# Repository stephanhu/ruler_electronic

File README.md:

# ruler_electronic
A 30cm ruler with some electronic stuff

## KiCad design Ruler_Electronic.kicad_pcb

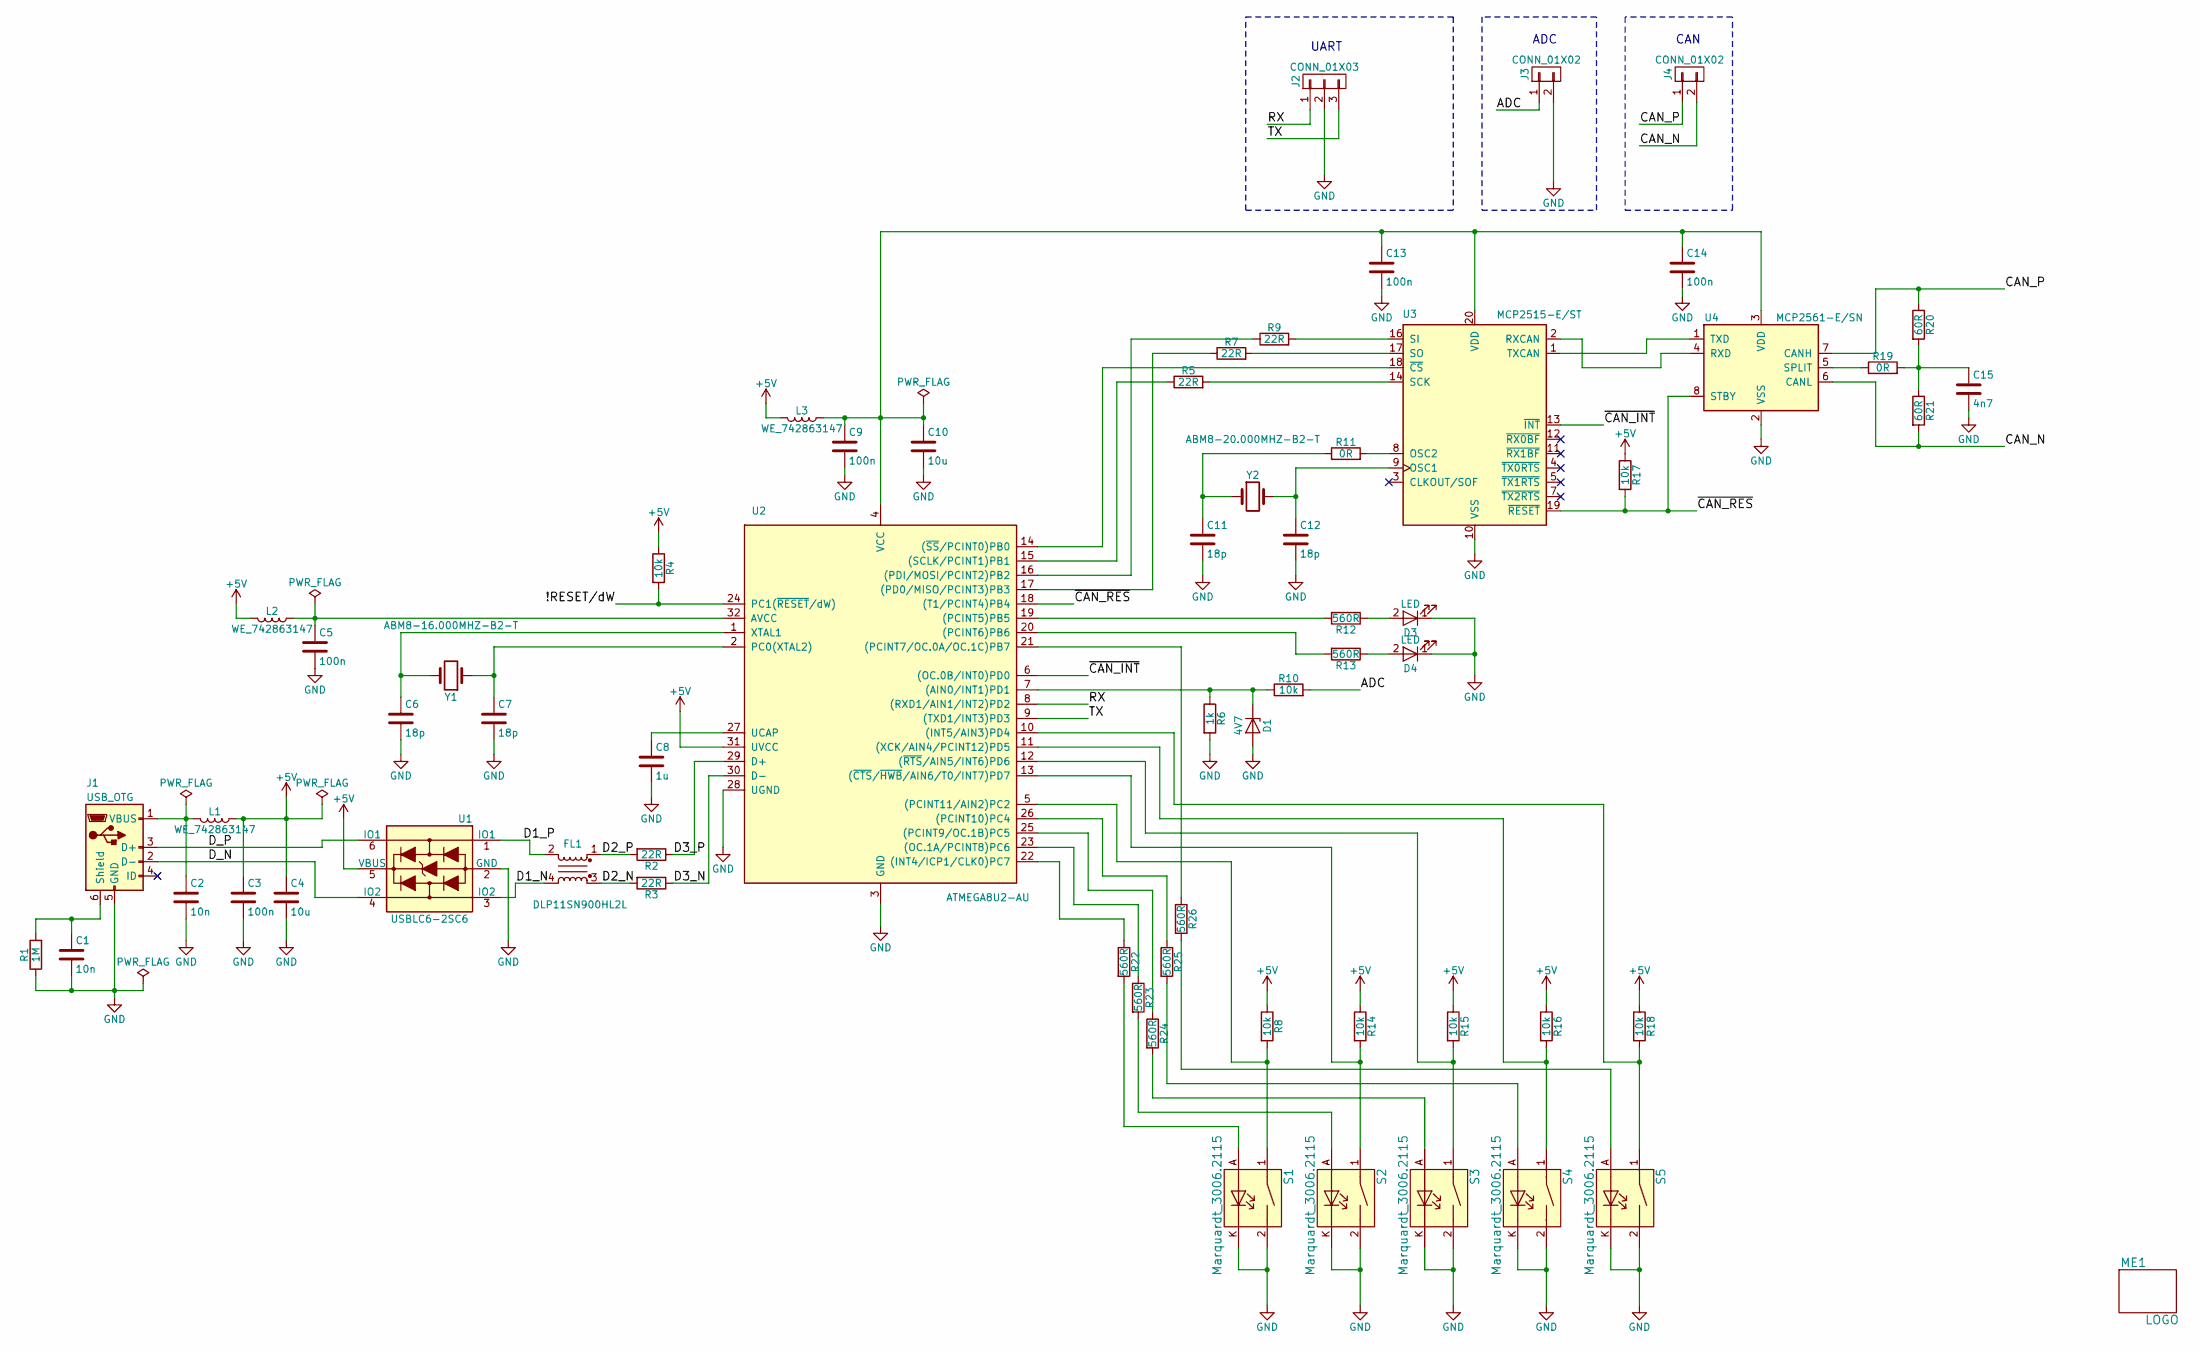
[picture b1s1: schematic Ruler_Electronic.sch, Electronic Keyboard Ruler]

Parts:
C1, C2: 10n; C_0603_HandSoldering
C3, C5, C9, C13, C14: 100n; C_0603_HandSoldering
C4, C10: 10u; C_0805_HandSoldering
C6, C7, C11, C12: 18p; C_0603_HandSoldering
C8: 1u; C_0805_HandSoldering
C15: 4n7; C_0603_HandSoldering
D1: 4V7; D_MELF_Handsoldering
D3, D4: LED; LED_0603_HandSoldering
FL1: DLP11SN900HL2L; L_Murata_DLP11S
J1: USB_OTG; USB_Mini-B
J2: CONN_01X03; Pin_Header_Angled_1x03_Pitch2.54mm
J3, J4: CONN_01X02; Pin_Header_Angled_1x02_Pitch2.54mm
L1, L2, L3: WE_742863147; L_0603_HandSoldering
ME1: LOGO; bytewerk_logo_15x13mm
R1: 1M; R_0603_HandSoldering
R2, R3, R5, R7, R9: 22R; R_0603_HandSoldering
R4, R8, R10, R14, R15, R16, R17, R18: 10k; R_0603_HandSoldering
R6: 1k; R_0603_HandSoldering
R11, R19: 0R; R_0603_HandSoldering
R12, R13, R22, R23, R24, R25, R26: 560R; R_0603_HandSoldering
R20, R21: 60R; R_0603_HandSoldering
S1, S2, S3, S4, S5: Marquardt_3006.2115; Marquardt_3006.2xxx
U1: USBLC6-2SC6; SOT-23-6
U2: ATMEGA8U2-AU; TQFP-32_7x7mm_Pitch0.8mm
U3: MCP2515-E/ST; TSSOP-20_4.4x6.5mm_Pitch0.65mm
U4: MCP2561-E/SN; SOIC-8_3.9x4.9mm_Pitch1.27mm
Y1: ABM8-16.000MHZ-B2-T; Crystal_SMD_Abracon_ABM8G-4pin_3.2x2.5mm
Y2: ABM8-20.000MHZ-B2-T; Crystal_SMD_Abracon_ABM8G-4pin_3.2x2.5mm

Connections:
+5V: C3.1, C4.1, L1.1, L2.2, L3.2, R4.1, R8.1, R14.1, R15.1, R16.1, R17.1, R18.1, U1.5 (VBUS), U2.31 (UVCC)
/!RESET/dW: R4.2, U2.24 (PC1(~RESET~/dW))
/ADC: J3.1, R10.2
/CAN_N: J4.2, R21.2, U4.6 (CANL)
/CAN_P: J4.1, R20.1, U4.7 (CANH)
/D1_N: FL1.4, U1.3 (IO2)
/D1_P: FL1.2, U1.1 (IO1)
/D2_N: FL1.3, R3.2
/D2_P: FL1.1, R2.2
/D3_N: R3.1, U2.30 (D-)
/D3_P: R2.1, U2.29 (D+)
/D_N: J1.2 (D-), U1.4 (IO2)
/D_P: J1.3 (D+), U1.6 (IO1)
/RX: J2.1, U2.8 ((RXD1/AIN1/INT2)PD2)
/TX: J2.3, U2.9 ((TXD1/INT3)PD3)
/~CAN_INT: U2.6 ((OC.0B/INT0)PD0), U3.13 (~INT)
/~CAN_RES: R17.2, U2.18 ((T1/PCINT4)PB4), U3.19 (~RESET), U4.8 (STBY)
GND: C1.2, C2.2, C3.2, C4.2, C5.2, C6.2, C7.2, C8.2, C9.2, C10.2, C11.2, C12.2, C13.2, C14.2, C15.2, D1.2 (A), D3.1 (K), D4.1 (K), J1.5 (GND), J2.2, J3.2, R1.1, R6.2, S1.2, S1.K, S2.2, S2.K, S3.2, S3.K, S4.2, S4.K, S5.2, S5.K, U1.2 (GND), U2.3 (GND), U2.28 (UGND), U3.10 (VSS), U4.2 (VSS)
unnamed: C1.1, J1.6 (Shield), R1.2
unnamed: C2.1, J1.1 (VBUS), L1.2
unnamed: C5.1, L2.1, U2.32 (AVCC)
unnamed: C6.1, U2.1 (XTAL1), Y1.2
unnamed: C7.1, U2.2 (PC0(XTAL2)), Y1.1
unnamed: C8.1, U2.27 (UCAP)
unnamed: C9.1, C10.1, C13.1, C14.1, L3.1, U2.4 (VCC), U3.20 (VDD), U4.3 (VDD)
unnamed: C11.1, R11.1, Y2.1
unnamed: C12.1, U3.9 (OSC1), Y2.2
unnamed: C15.1, R19.2, R20.2, R21.1
unnamed: D1.1 (K), R6.1, R10.1, U2.7 ((AIN0/INT1)PD1)
unnamed: D3.2 (A), R12.1
unnamed: D4.2 (A), R13.1
unnamed: R5.1, U2.15 ((SCLK/PCINT1)PB1)
unnamed: R5.2, U3.14 (SCK)
unnamed: R7.1, U2.17 ((PD0/MISO/PCINT3)PB3)
unnamed: R7.2, U3.17 (SO)
unnamed: R8.2, S1.1, U2.5 ((PCINT11/AIN2)PC2)
unnamed: R9.1, U2.16 ((PDI/MOSI/PCINT2)PB2)
unnamed: R9.2, U3.16 (SI)
unnamed: R11.2, U3.8 (OSC2)
unnamed: R12.2, U2.19 ((PCINT5)PB5)
unnamed: R13.2, U2.20 ((PCINT6)PB6)
unnamed: R14.2, S2.1, U2.13 ((~CTS~/~HWB~/AIN6/T0/INT7)PD7)
unnamed: R15.2, S3.1, U2.12 ((~RTS~/AIN5/INT6)PD6)
unnamed: R16.2, S4.1, U2.11 ((XCK/AIN4/PCINT12)PD5)
unnamed: R18.2, S5.1, U2.10 ((INT5/AIN3)PD4)
unnamed: R19.1, U4.5 (SPLIT)
unnamed: R22.1, U2.22 ((INT4/ICP1/CLK0)PC7)
unnamed: R22.2, S1.A
unnamed: R23.1, U2.23 ((OC.1A/PCINT8)PC6)
unnamed: R23.2, S2.A
unnamed: R24.1, U2.25 ((PCINT9/OC.1B)PC5)
unnamed: R24.2, S3.A
unnamed: R25.1, U2.26 ((PCINT10)PC4)
unnamed: R25.2, S4.A
unnamed: R26.1, U2.21 ((PCINT7/OC.0A/OC.1C)PB7)
unnamed: R26.2, S5.A
unnamed: U2.14 ((~SS~/PCINT0)PB0), U3.18 (~CS)
unnamed: U3.1 (TXCAN), U4.1 (TXD)
unnamed: U3.2 (RXCAN), U4.4 (RXD)

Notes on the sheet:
UART
ADC
CAN

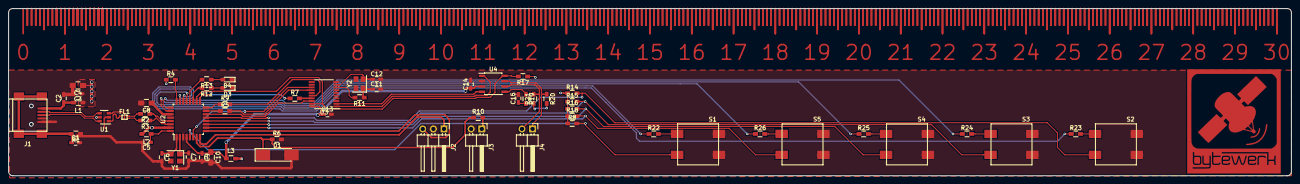
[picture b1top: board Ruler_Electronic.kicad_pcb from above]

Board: 2 copper layers, 307.0 x 40.0 mm, 63 parts (0 on the bottom side), 59 nets.

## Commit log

2017-10-11 init
2017-10-11 added submodule kicad libs
2017-10-14 finished layout
2017-10-25 blubb
2017-10-25 update lib
2017-10-25 rename
2017-10-25 change in layout and new logo
